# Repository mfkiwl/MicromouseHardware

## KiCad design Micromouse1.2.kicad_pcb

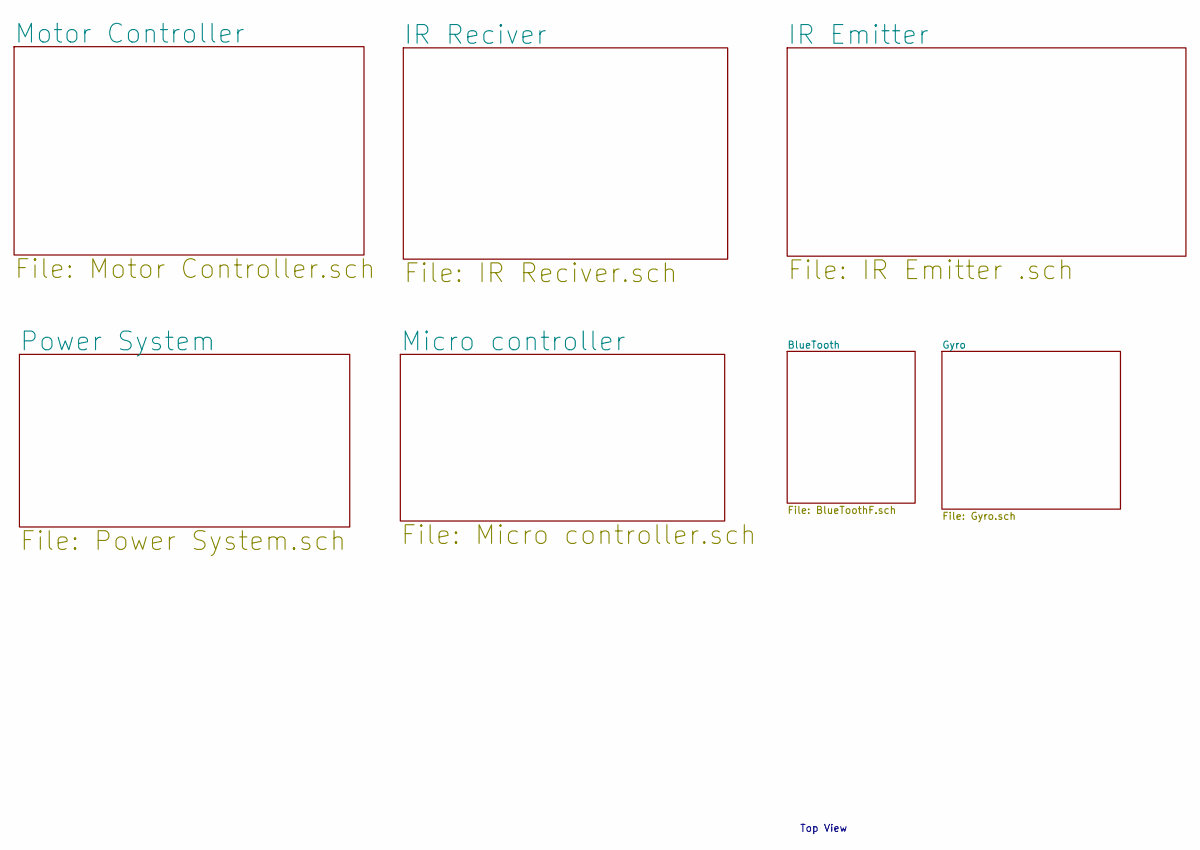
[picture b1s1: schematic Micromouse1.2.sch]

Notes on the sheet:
Top View

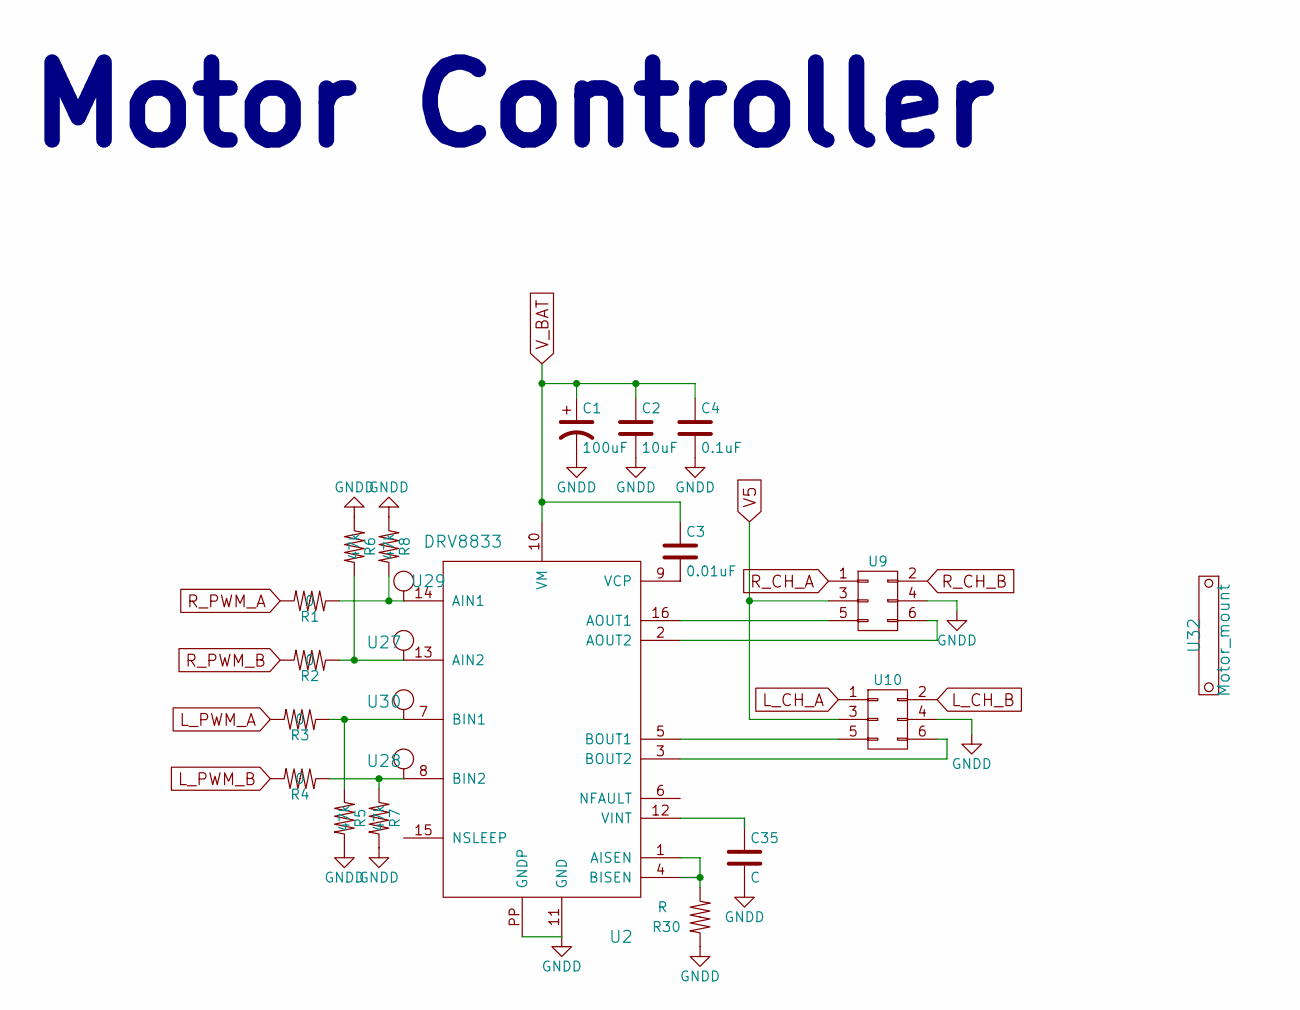
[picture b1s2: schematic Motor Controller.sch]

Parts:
C1: 100uF
C2: 10uF; C_0805
C3: 0.01uF
C4: 0.1uF; C_0603
C35: C; C_0402
R1, R2, R3, R4: 0; C_0402
R5, R6, R7, R8: 47k; C_0402
R30: R
U2: DRV8833
U9, U10: CONN_02X03
U27, U28, U29, U30: Test_Point
U32: Motor_mount

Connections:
GNDD: C1.2, C2.2, C4.2, C35.2, R5.2, R6.1, R7.2, R8.1, R30.2, U2.11 (GND), U2.PP (GNDP), U9.4, U10.4; also elsewhere on the board
L_CH_A: U10.1
L_CH_B: U10.2
L_PWM_A: R3.2; also elsewhere on the board
L_PWM_B: R4.2; also elsewhere on the board
unnamed: C3.2, U2.9 (VCP)
unnamed: C35.1, U2.12 (VINT)
unnamed: R1.1, R8.2, U2.14 (AIN1), U29.1
unnamed: R2.1, R6.2, U2.13 (AIN2), U27.1
unnamed: R3.1, R5.1, U2.7 (BIN1), U30.1
unnamed: R4.1, R7.1, U2.8 (BIN2), U28.1
unnamed: R30.1, U2.1 (AISEN), U2.4 (BISEN)
unnamed: U2.2 (AOUT2), U9.6
unnamed: U2.16 (AOUT1), U9.5
unnamed: U2.5 (BOUT1), U10.5
unnamed: U2.3 (BOUT2), U10.6
R_CH_A: U9.1
R_CH_B: U9.2; also elsewhere on the board
R_PWM_A: R1.2; also elsewhere on the board
R_PWM_B: R2.2; also elsewhere on the board
V5: U9.3, U10.3; also elsewhere on the board
V_BAT: C1.1, C2.1, C3.1, C4.1, U2.10 (VM); also elsewhere on the board

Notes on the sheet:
Motor Controller

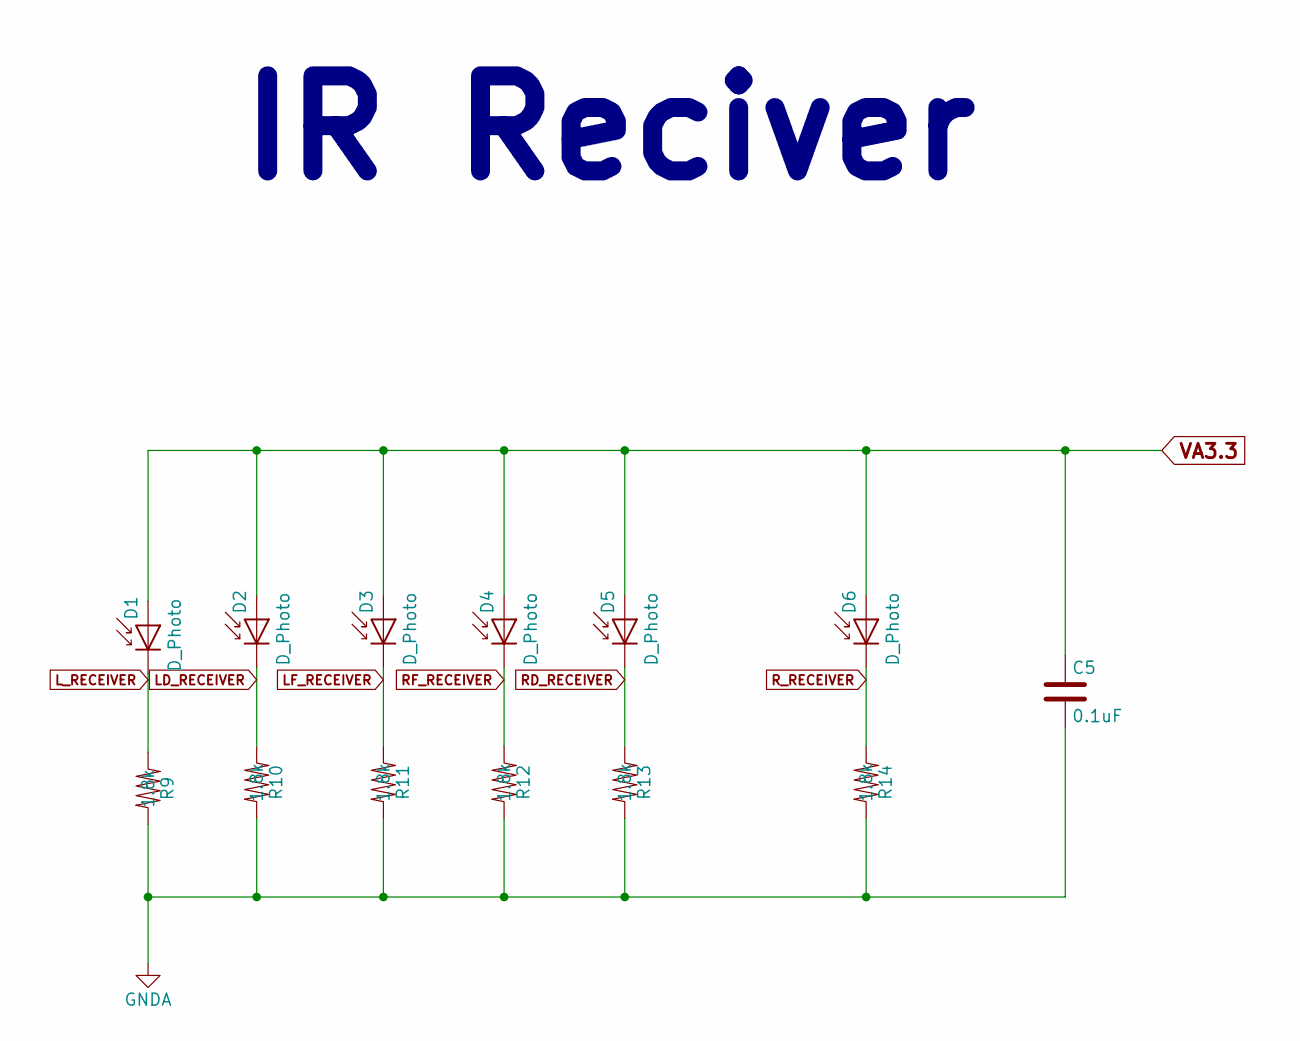
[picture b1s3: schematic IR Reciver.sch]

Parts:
C5: 0.1uF; C_0603
D1, D2, D3, D4, D5, D6: D_Photo; IR_Reciver
R9, R10, R11, R12, R13, R14: 1.8k; R_0603

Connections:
GNDA: C5.2, R9.2, R10.2, R11.2, R12.2, R13.2, R14.2; also elsewhere on the board
LD_RECEIVER: D2.1 (K), R10.1; also elsewhere on the board
LF_RECEIVER: D3.1 (K), R11.1; also elsewhere on the board
L_RECEIVER: D1.1 (K), R9.1; also elsewhere on the board
RD_RECEIVER: D5.1 (K), R13.1; also elsewhere on the board
RF_RECEIVER: D4.1 (K), R12.1; also elsewhere on the board
R_RECEIVER: D6.1 (K), R14.1; also elsewhere on the board
VA3.3: C5.1, D1.2 (A), D2.2 (A), D3.2 (A), D4.2 (A), D5.2 (A), D6.2 (A); also elsewhere on the board

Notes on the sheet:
IR Reciver

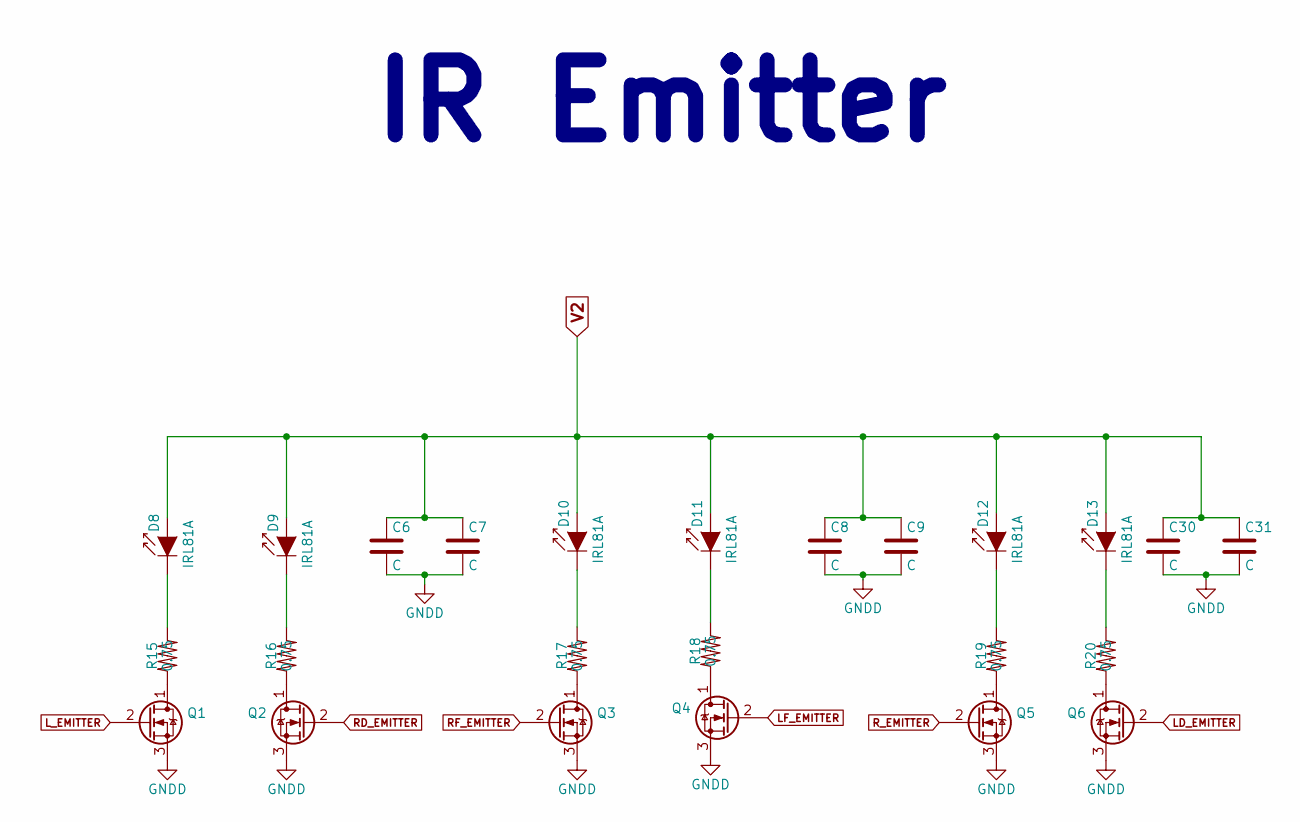
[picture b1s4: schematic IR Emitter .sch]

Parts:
C6, C7, C8, C9, C30, C31: C; C_0603
D8, D9, D10, D11, D12, D13: IRL81A; IR_Emitter
Q1, Q2, Q3, Q4, Q5, Q6: Q_NMOS_DGS; DMG1012UW
R15, R16, R17, R18, R19, R20: 0.75; C_0402

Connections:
GNDD: C6.2, C7.2, C8.2, C9.2, C30.2, C31.2, Q1.3 (S), Q2.3 (S), Q3.3 (S), Q4.3 (S), Q5.3 (S), Q6.3 (S); also elsewhere on the board
LD_EMITTER: Q6.2 (G)
LF_EMITTER: Q4.2 (G)
L_EMITTER: Q1.2 (G)
unnamed: D8.1 (K), R15.2
unnamed: D9.1 (K), R16.2
unnamed: D10.1 (K), R17.2
unnamed: D11.1 (K), R18.2
unnamed: D12.1 (K), R19.2
unnamed: D13.1 (K), R20.2
unnamed: Q1.1 (D), R15.1
unnamed: Q2.1 (D), R16.1
unnamed: Q3.1 (D), R17.1
unnamed: Q4.1 (D), R18.1
unnamed: Q5.1 (D), R19.1
unnamed: Q6.1 (D), R20.1
RD_EMITTER: Q2.2 (G)
RF_EMITTER: Q3.2 (G)
R_EMITTER: Q5.2 (G)
V2: C6.1, C7.1, C8.1, C9.1, C30.1, C31.1, D8.2 (A), D9.2 (A), D10.2 (A), D11.2 (A), D12.2 (A), D13.2 (A); also elsewhere on the board

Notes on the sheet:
IR Emitter

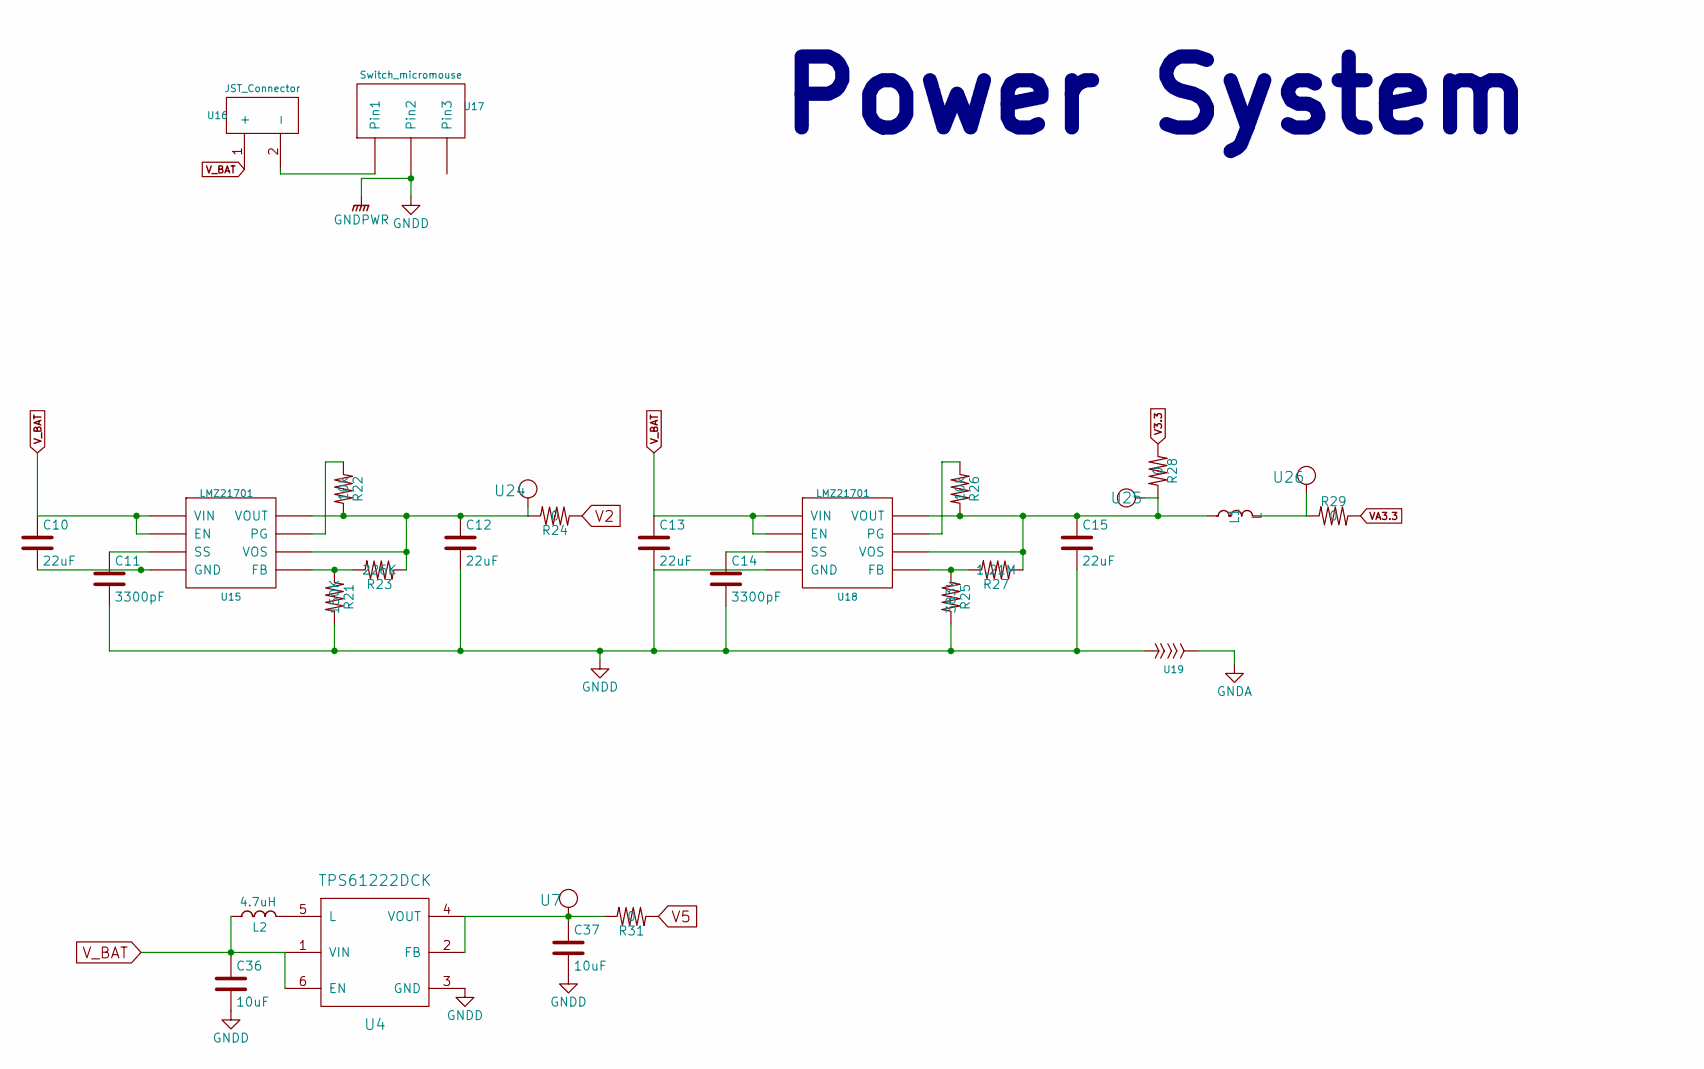
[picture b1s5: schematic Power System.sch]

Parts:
C10, C12: 22uF; R_0805
C11, C14: 3300pF; C_0402
C13, C15: 22uF; C_0805
C36: 10uF; C_0603
C37: 10uF; C_0805
L1: L; L_0603
L2: 4.7uH; Neosid_Inductor_SM-NE29_SMD1008
R21: 150K; R_0402
R22, R26: 10k; R_0402
R23: 226K; R_0402
R24, R28, R29, R31: 0; R_0603
R25: 383k; R_0402
R27: 1.21M; R_0402
U4: TPS61222DCK
U7, U24, U25, U26: Test_Point
U15, U18: LMZ21701
U16: JST_Connector
U17: Switch_micromouse; Switch_battery
U19: splitter; spliter

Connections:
GNDA: U19.2; also elsewhere on the board
GNDD: C11.2, C12.2, C13.2, C14.2, C15.2, C36.2, C37.2, R21.2, R25.2, U4.3 (GND), U17.2 (Pin2), U18.5 (GND), U19.1; also elsewhere on the board
unnamed: C10.2, U15.5 (GND)
unnamed: C11.1, U15.1 (SS)
unnamed: C12.1, R22.2, R23.1, R24.2, U15.4 (VOUT), U15.6 (VOS), U24.1
unnamed: C14.1, U18.1 (SS)
unnamed: C15.1, L1.1, R26.2, R27.1, R28.2, U18.4 (VOUT), U18.6 (VOS), U25.1
unnamed: C37.1, R31.2, U4.2 (FB), U4.4 (VOUT), U7.1
unnamed: L1.2, R29.1, U26.1
unnamed: L2.2, U4.5 (L)
unnamed: R21.1, R23.2, U15.2 (FB)
unnamed: R22.1, U15.3 (PG)
unnamed: R25.1, R27.2, U18.2 (FB)
unnamed: R26.1, U18.3 (PG)
unnamed: U16.2 (-), U17.1 (Pin1)
V2: R24.1; also elsewhere on the board
V3.3: R28.1
V5: R31.1; also elsewhere on the board
VA3.3: R29.2; also elsewhere on the board
V_BAT: C10.1, C13.1, C36.1, L2.1, U4.1 (VIN), U4.6 (EN), U15.7 (EN), U15.8 (VIN), U16.1 (+), U18.7 (EN), U18.8 (VIN); also elsewhere on the board

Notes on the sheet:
Power System

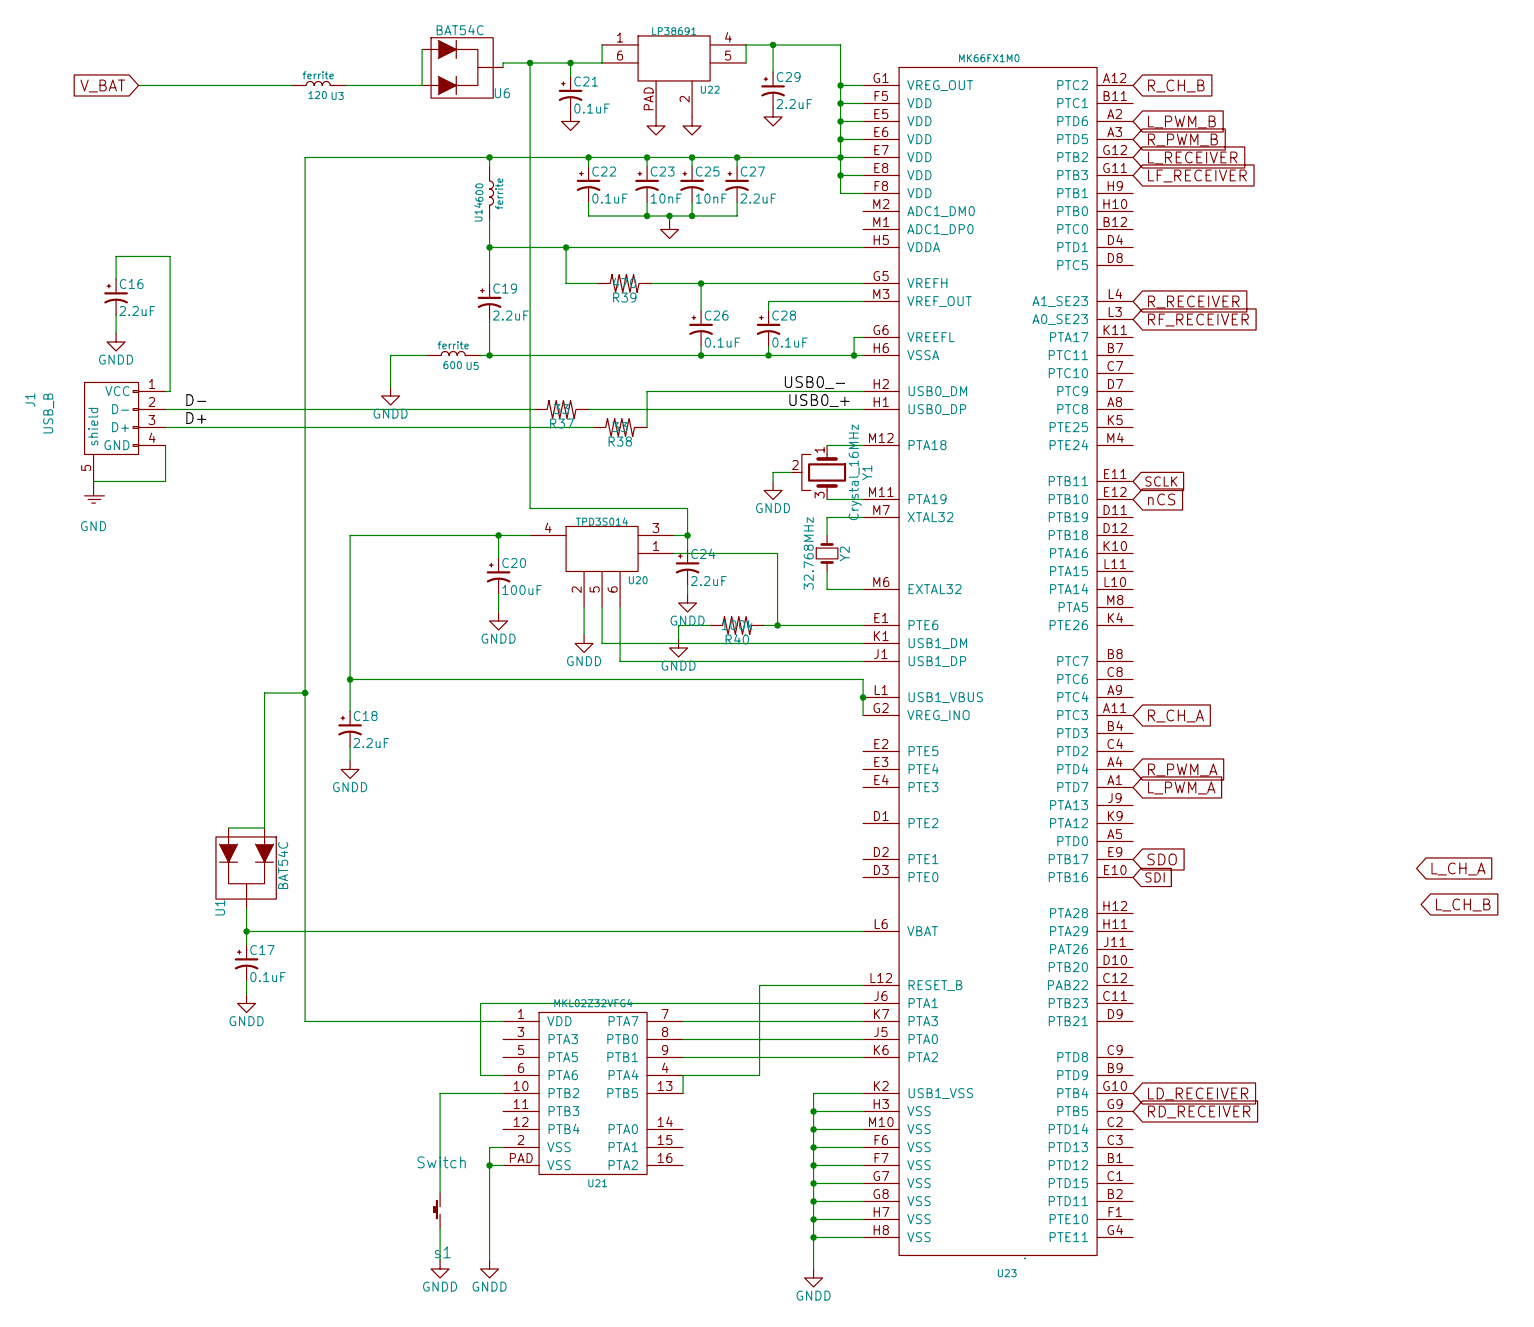
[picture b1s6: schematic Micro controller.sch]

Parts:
C16, C18, C19, C24, C27, C29: 2.2uF; C_0603
C17, C21, C22, C26, C28: 0.1uF; C_0402
C20: 100uF; C_1206
C23, C25: 10nF; C_0402
J1: USB_B; USB_Micro-B
R37, R38: 33; R_0402
R39: 470; R_0402
R40: 100k; R_0402
U1, U6: BAT54C; PMEG4010_DIODE
U3: ferrite; C_0603
U5, U14: ferrite; R_0402
U20: TPD3S014
U21: MKL02Z32VFG4
U22: LP38691
U23: MK66FX1M0; Microcontroller
Y1: Crystal_16MHz; 16Mhz_crystal
Y2: 32.768MHz; 32.768_CRYSTAL
s1: Switch; Switch_teensy

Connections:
/Micro controller/D+: J1.3 (D+), R38.2
/Micro controller/D-: J1.2 (D-), R37.2
/Micro controller/USB0_+: R37.1, U23.H1 (USB0_DP)
/Micro controller/USB0_-: R38.1, U23.H2 (USB0_DM)
GNDD: C16.2, C17.2, C18.2, C20.2, C21.2, C22.2, C23.2, C24.2, C25.2, C27.2, C29.2, R40.2, U5.1, U20.2, U21.2 (VSS), U21.PAD (VSS), U22.2, U22.PAD, U23.F6 (VSS), U23.F7 (VSS), U23.G7 (VSS), U23.G8 (VSS), U23.H3 (VSS), U23.H7 (VSS), U23.H8 (VSS), U23.K2 (USB1_VSS), U23.M10 (VSS), Y1.2, s1.2; also elsewhere on the board
LD_RECEIVER: U23.G10 (PTB4); also elsewhere on the board
LF_RECEIVER: U23.G11 (PTB3); also elsewhere on the board
L_PWM_A: U23.A1 (PTD7); also elsewhere on the board
L_PWM_B: U23.A2 (PTD6); also elsewhere on the board
L_RECEIVER: U23.G12 (PTB2); also elsewhere on the board
unnamed: C16.1, J1.1 (VCC)
unnamed: C17.1, U1.3, U23.L6 (VBAT)
unnamed: C18.1, C20.1, U20.4, U23.G2 (VREG_INO), U23.L1 (USB1_VBUS)
unnamed: C19.1, R39.2, U14.2, U23.H5 (VDDA)
unnamed: C19.2, C26.2, C28.2, U5.2, U23.G6 (VREEFL), U23.H6 (VSSA)
unnamed: C21.1, C24.1, U6.3, U20.3, U22.1, U22.6
unnamed: C22.1, C23.1, C25.1, C27.1, C29.1, U1.1 (A), U1.2 (A), U14.1, U21.1 (VDD), U22.4, U22.5, U23.E5 (VDD), U23.E6 (VDD), U23.E7 (VDD), U23.E8 (VDD), U23.F5 (VDD), U23.F8 (VDD), U23.G1 (VREG_OUT)
unnamed: C26.1, R39.1, U23.G5 (VREFH)
unnamed: C28.1, U23.M3 (VREF_OUT)
unnamed: J1.4 (GND), J1.5 (shield)
unnamed: R40.1, U20.1, U23.E1 (PTE6)
unnamed: U3.2, U6.1 (A), U6.2 (A)
unnamed: U20.5, U23.K1 (USB1_DM)
unnamed: U20.6, U23.J1 (USB1_DP)
unnamed: U21.6 (PTA6), U23.J6 (PTA1)
unnamed: U21.7 (PTA7), U23.K7 (PTA3)
unnamed: U21.8 (PTB0), U23.J5 (PTA0)
unnamed: U21.9 (PTB1), U23.K6 (PTA2)
unnamed: U21.10 (PTB2), s1.1
unnamed: U21.4 (PTA4), U21.13 (PTB5), U23.L12 (RESET_B)
unnamed: U23.M6 (EXTAL32), Y2.2
unnamed: U23.M7 (XTAL32), Y2.1
unnamed: U23.M11 (PTA19), Y1.3
unnamed: U23.M12 (PTA18), Y1.1
RD_RECEIVER: U23.G9 (PTB5); also elsewhere on the board
RF_RECEIVER: U23.L3 (A0_SE23); also elsewhere on the board
R_CH_B: U23.A5 (PTD0); also elsewhere on the board
R_PWM_A: U23.A4 (PTD4); also elsewhere on the board
R_PWM_B: U23.A3 (PTD5); also elsewhere on the board
R_RECEIVER: U23.L4 (A1_SE23); also elsewhere on the board
SCLK: U23.E11 (PTB11); also elsewhere on the board
SDI: U23.E10 (PTB16); also elsewhere on the board
SDO: U23.E9 (PTB17); also elsewhere on the board
V_BAT: U3.1; also elsewhere on the board
nCS: U23.E12 (PTB10); also elsewhere on the board

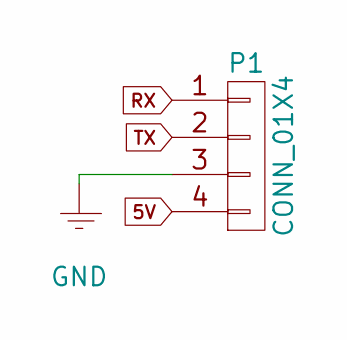
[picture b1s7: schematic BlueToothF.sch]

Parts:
P1: CONN_01X4; Socket_Strip_Straight_1x04_Pitch2.54mm

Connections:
5V: P1.4
RX: P1.1
TX: P1.2

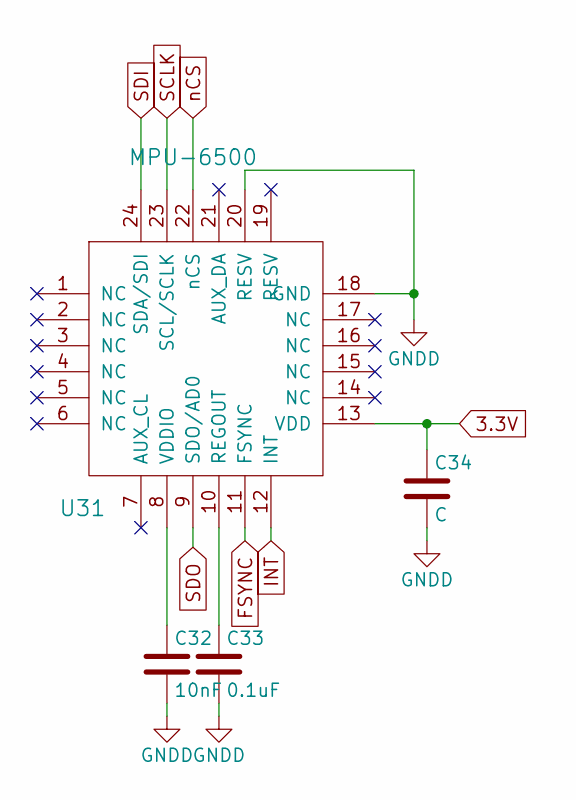
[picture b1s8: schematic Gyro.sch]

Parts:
C32: 10nF; C_0603
C33: 0.1uF; C_0603
C34: C; C_0603
U31: MPU-6500

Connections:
3.3V: C34.1, U31.13 (VDD)
FSYNC: U31.11 (FSYNC)
GNDD: C32.2, C33.2, C34.2, U31.18 (GND), U31.20 (RESV); also elsewhere on the board
INT: U31.12 (INT)
unnamed: C32.1, U31.8 (VDDIO)
unnamed: C33.1, U31.10 (REGOUT)
SCLK: U31.23 (SCL/SCLK); also elsewhere on the board
SDI: U31.24 (SDA/SDI); also elsewhere on the board
SDO: U31.9 (SDO/AD0); also elsewhere on the board
nCS: U31.22 (nCS); also elsewhere on the board

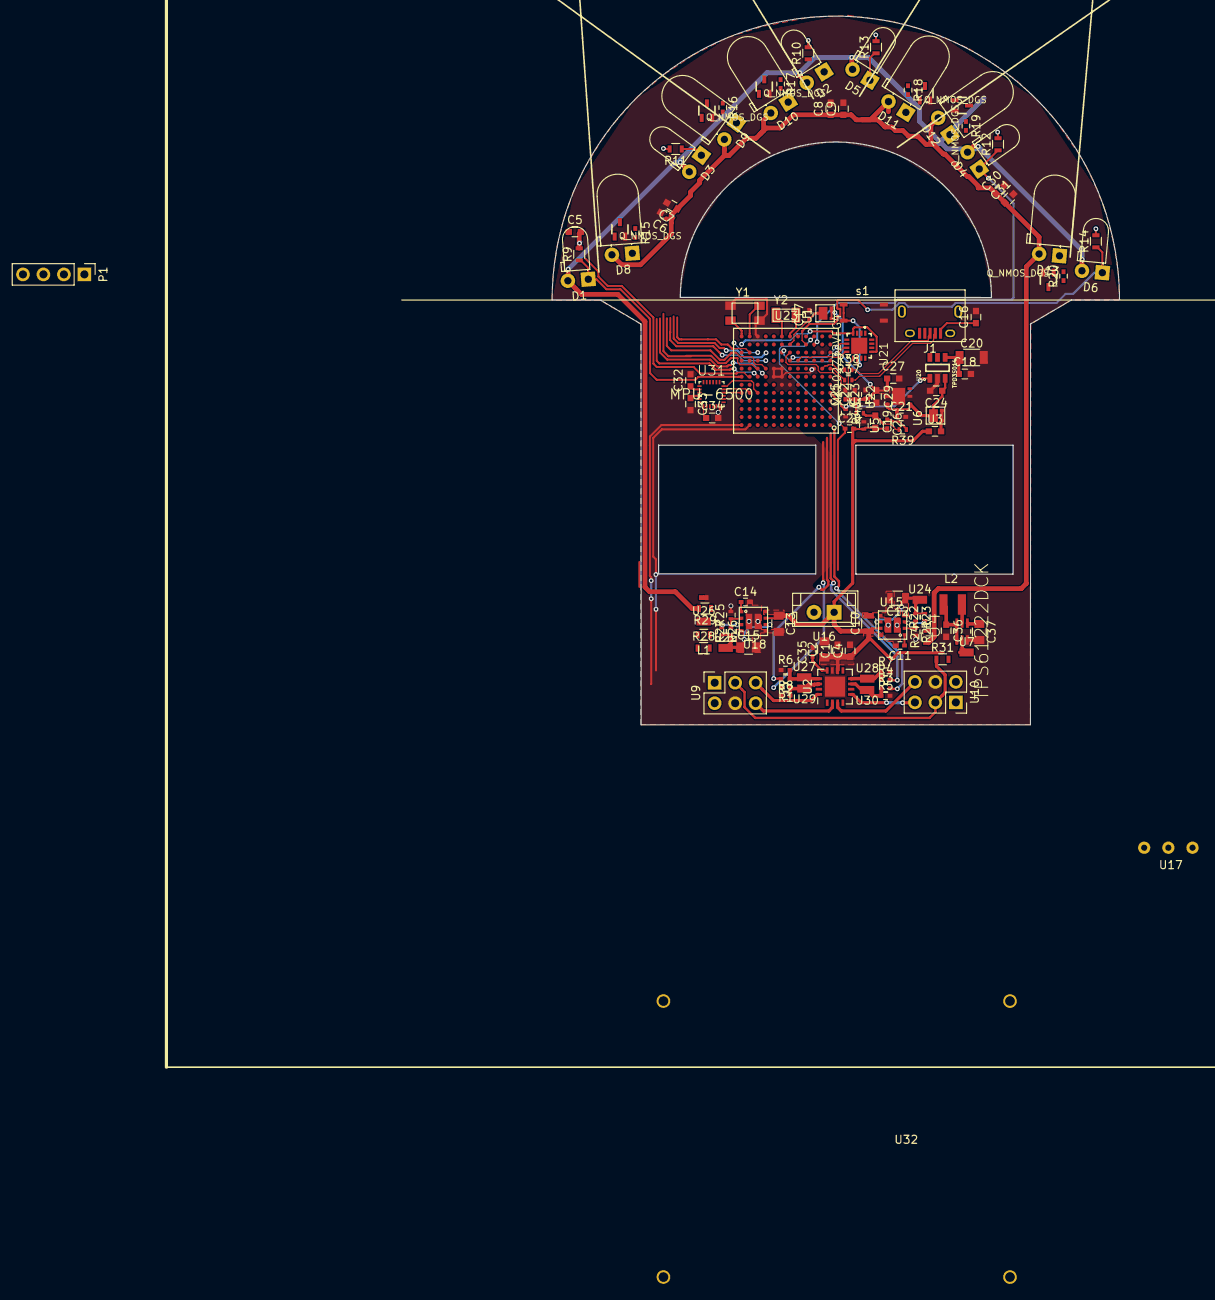
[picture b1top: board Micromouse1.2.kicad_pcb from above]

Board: 2 copper layers, 70.4 x 87.9 mm, 123 parts (0 on the bottom side), 87 nets.

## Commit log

2017-06-06 Created the Motor Controller schematic
    Added
    -motor controller schematic
    -Tc442, the H-brigh and 2X3 header library
2017-06-18 Created teensy schematics
    -added MK66FX1M0 schematic
    -added LP38691 linear regulator
    -added PMEG4010CPA
2017-06-20 started wiring up the teensy schematic
2017-06-21 finished the microcontroller connection
    Finished the microcontrollers wiring up with out the pins.
2017-06-22 changed the spliter simbole
2017-06-22 Motor Ground, isolation resistor
    I added the Motor ground symbols instead of using global label for
    clarity. I also added double to 0 ohm resistors for isolation purposes.
2017-06-23 Created footprint for DC DC converter
2017-06-23 Corrected LMZ21701 REF position
2017-06-23 created footprint for linear requlator
    added footprint for microcontroller linear requlator
2017-06-27 Added data sheets
    Added data she for
    - teensy diode
    - 5V linear voltage regulator
    - motor 2x3 header
    -teensy ferrite
    -leds
2017-07-08 added more footprints
    added more footprints such as the microcontroller programer and voltage regualtor
2017-07-09 temp commit
2017-07-25 fixed the mergre conflicts from the adding datasheet commite
2017-07-25 added IR-Emitter and IR_Reciver footprint
2017-07-25 resotred micro controller schematic to the older complited version
2017-07-28 Added footprints for diode and both 16MHz and 32.678Mhz crystal
2017-08-01 added Bluetooth schmatic
2017-08-01 removed SD Card
2017-08-02 generated a netlist
    filled the teensy components with 0402 size untill i find out more info.
    Starting to do PCB layout.
2017-09-03 Added MPU-6500
2017-09-24 finished floor planning
    -replaced the TC4427 and H brige by a single DRV8833 chip
2017-10-08 made 3D wheel and Tire setup
2017-10-19 Change of direction
    - I am changing my MCU from mk66fx1m0vmd18 to mk20dx256vlh7 as the QFN package pcb layout is too expensive to manufacture and the 144 LQFP is takes too much real estate
2017-10-19 finished the schematics of the new mcu
    -built a new design for MK20DX64VLH7 MCU
2017-10-25 changed the MCU to MK20DX256VLH7
    -changed the MCU to MK20DX256VLH7
    -This branch is deprciated as I am changing back to the K66 series MCU
2017-10-25 added TPS61222DCK boost converter
    -added TPS61222DCK boost converter for 5V input of the encoder
2017-10-25 layedout the boost converter
    -layedout the boost converter
    -rearranged the motor controller layout
    -cuted some pcb from the center front to reduce the weight(lower weight higher turn speed)
2017-10-26 wired up the MCU
    -wired up the mcu to the gyro, motor controller.
2017-12-09 Rev 1.0 done
2017-12-09 added isolated island underneath the 16Mhz Crystal
2017-12-29 fixed the unconnected teensy bootloader chip
2018-01-06 Fixed the broken 2Volt regulator output
2018-02-12 Added some media fiels
2018-02-12 Revert "Added some media fiels"
    This reverts commit 84cf00991dfa557b7e901656171e370188c900f8.
2018-02-12 Revert "Added some media fiels"
2018-02-12 included more description about the repository
